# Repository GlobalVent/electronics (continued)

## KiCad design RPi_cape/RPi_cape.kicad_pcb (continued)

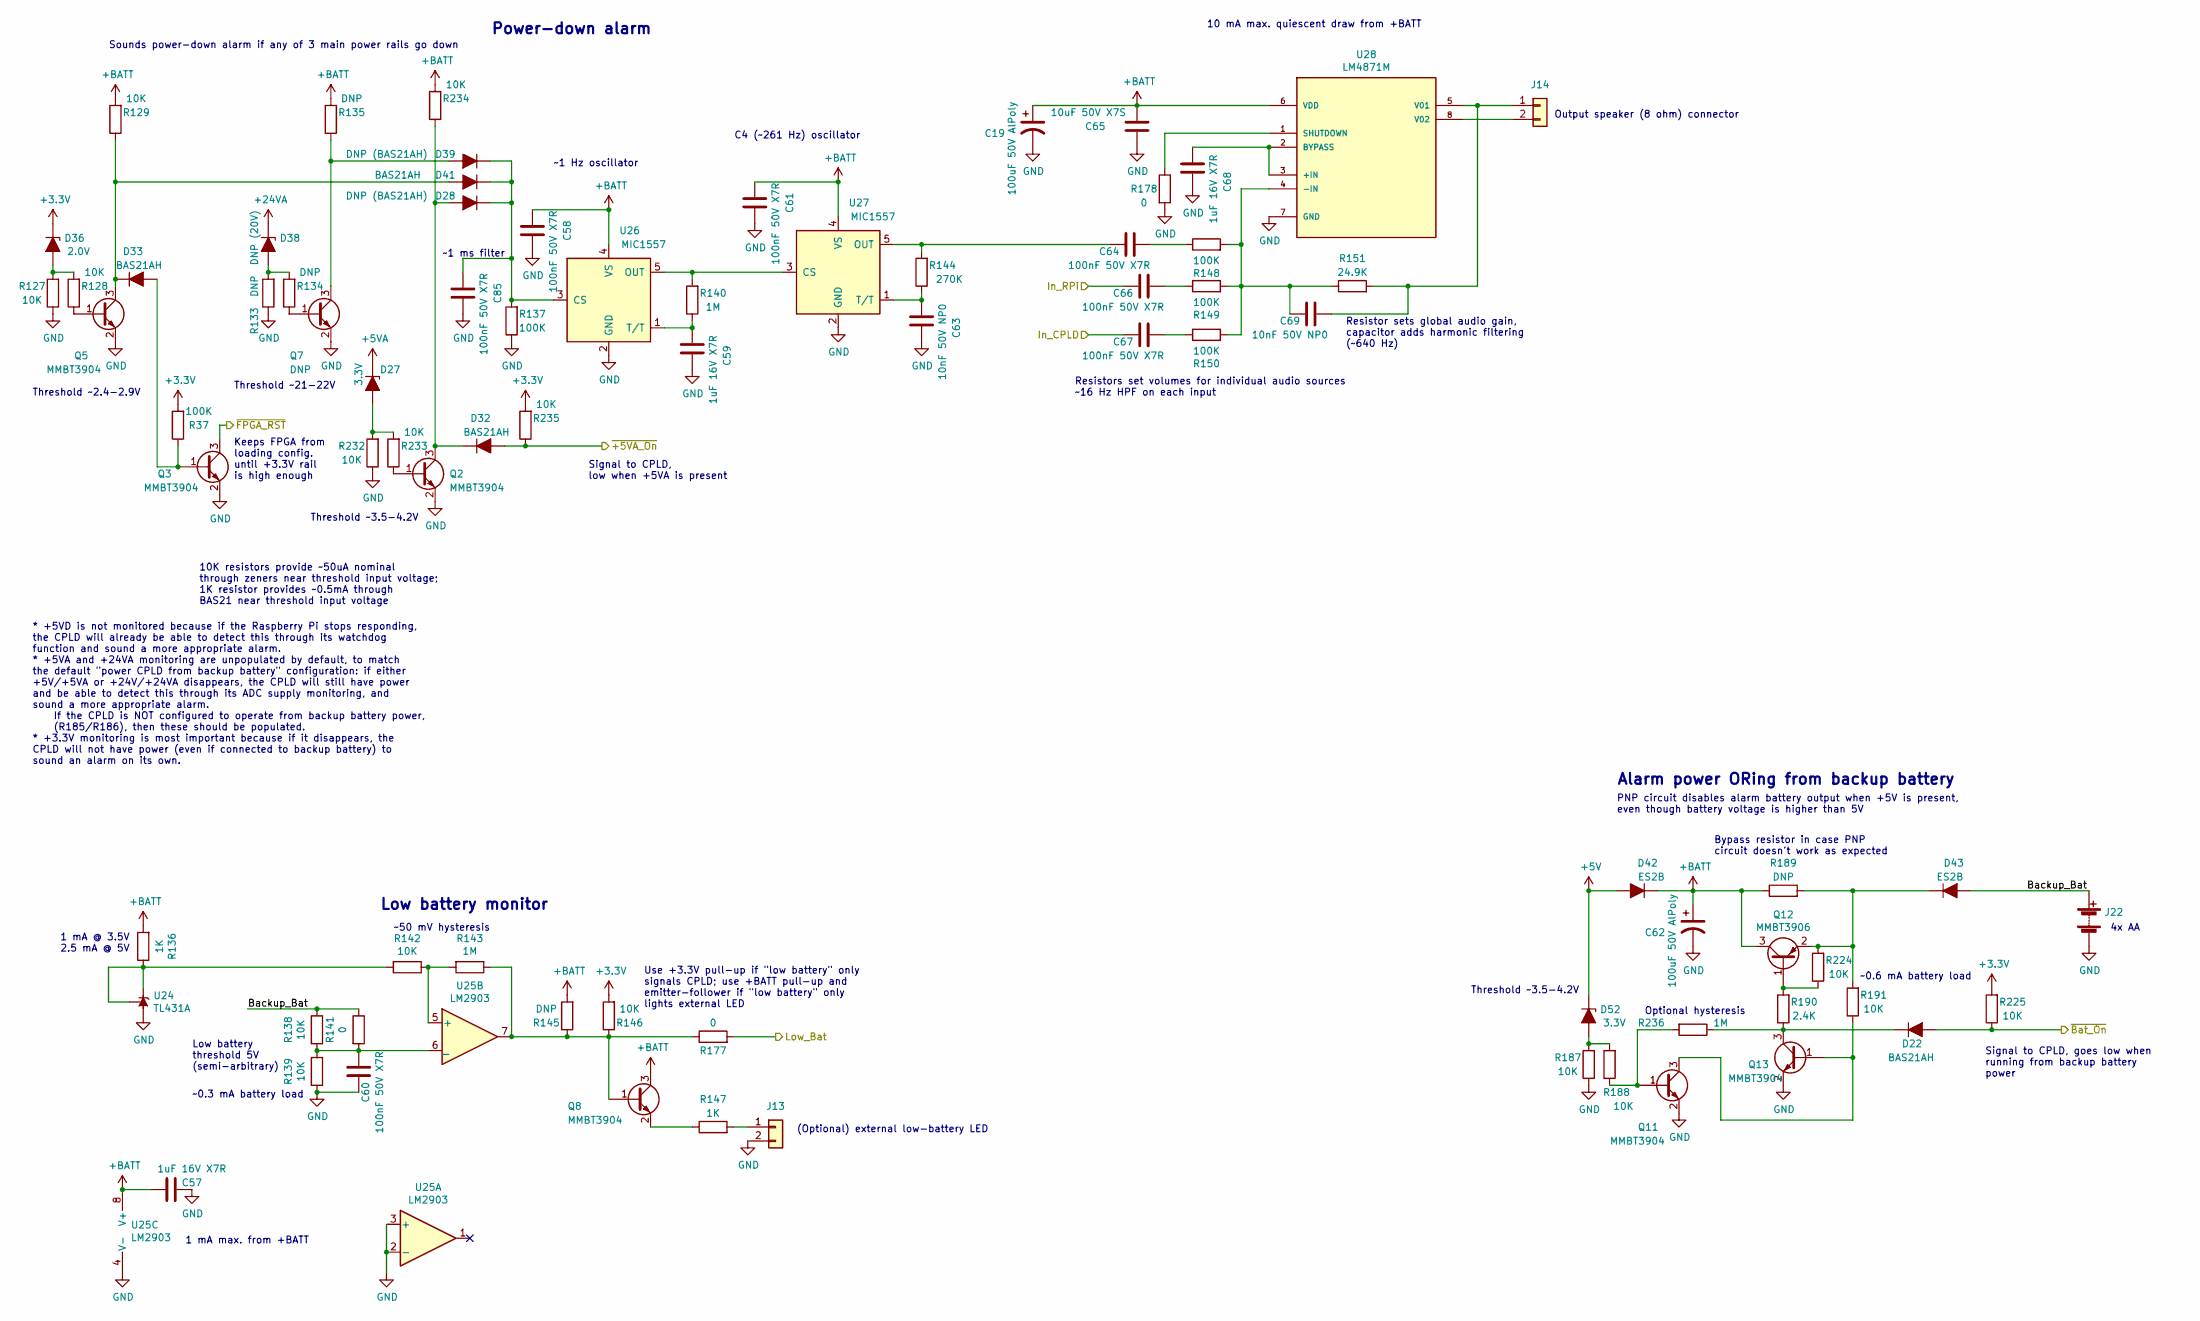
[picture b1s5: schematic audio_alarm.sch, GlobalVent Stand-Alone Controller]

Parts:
C19, C62: 100uF 50V AlPoly; CP_Elec_10x10.5; Part Number EEH-ZC1H101P
C57, C59, C68: 1uF 16V X7R; C_0805_2012Metric; Part Number C0805C105K4RACTU
C58, C60, C61, C64, C66, C67, C85: 100nF 50V X7R; C_0603_1608Metric; Part Number 06035C104JAT2A
C63, C69: 10nF 50V NP0; C_0603_1608Metric; Part Number GRM1885C1H103JA01D
C65: 10uF 50V X7S; C_1210_3225Metric; Part Number GCM32EC71H106KA03L
D22, D32, D33, D41: BAS21AH; D_SOD-323; Part Number BAS21AHT1G
D27, D52: 3.3V; D_SOD-123; Part Number MMSZ4684T1G
D28, D39: DNP (BAS21AH); D_SOD-323; Part Number BAS21AHT1G
D36: 2.0V; D_SOD-123; Part Number MMSZ4679T1G
D38: DNP (20V); D_SOD-123; Part Number MMSZ4707T1G
D42, D43: ES2B; D_SMA; Part Number ES2G-E3/52T
J13, J14: Conn_01x02; Connector_Spring_Phoenix_1985195; Part Number 1985195
J22: Conn_01x02; Connector_Spring_Phoenix_1985195; Part Number 9185195
Q2, Q3, Q5, Q8, Q11, Q13: MMBT3904; SOT-23; Part Number MMBT3904-7-F
Q7: DNP; SOT-23
Q12: MMBT3906; SOT-23; Part Number MMBT3906,215
R37, R137, R148, R149, R150: 100K; R_1206_3216Metric; Part Number RK73H2BTTD1003F
R127, R128, R129, R138, R139, R142, R146, R187, R188, R191, R224, R225, R232, R233, R234, R235: 10K; R_1206_3216Metric; Part Number RK73H2BTTD1002F
R133, R134, R135, R145, R189: DNP; R_1206_3216Metric
R136, R147: 1K; R_1206_3216Metric; Part Number RK73H2BTTD1001F
R140, R143, R236: 1M; R_1206_3216Metric; Part Number RK73H2BTTD1004F
R141, R177, R178: 0; R_1206_3216Metric; Part Number ERJ-8GEY0R00V
R144: 270K; R_1206_3216Metric; Part Number RK73H2BTTD2703F
R151: 24.9K; R_1206_3216Metric; Part Number RK73H2BTTD2492F
R190: 2.4K; R_1206_3216Metric; Part Number RK73H2BTTD2401F
U24: TL431A; SOT-23; Part Number TL431AQDBZR,215
U25: LM2903; VSSOP-8_3.0x3.0mm_P0.65mm; Part Number LM2903DGKR
U26, U27: MIC1557; SOT-23-5; Part Number MIC1557YM5-TR
U28: LM4871M; SOIC-8_3.9x4.9mm_P1.27mm; Part Number LM4871MX/NOPB

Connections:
+3V3: D36.1 (K), R37.2, R146.2, R225.2, R235.2; also elsewhere on the board
+5V: D42.2 (A), D52.1 (K); also elsewhere on the board
+24VA: D38.1 (K); also elsewhere on the board
+BATT: C19.1, C57.2, C58.2, C61.2, C62.1, C65.1, D42.1 (K), Q8.3 (C), Q12.3 (C), R129.2, R135.2, R136.2, R145.2, R189.1, R234.2, U25.8 (V+), U26.4 (VS), U27.4 (VS), U28.6 (VDD); also elsewhere on the board
/Auditory Alarm/Backup_Bat: D43.2 (A), J22.1 (+), R138.1, R141.1
/Auditory Alarm/Low_Bat: R177.2; also elsewhere on the board
/Auditory Alarm/~+5VA_On: D32.2 (A), R235.1; also elsewhere on the board
/Auditory Alarm/~Bat_On: D22.2 (A), R225.1; also elsewhere on the board
/Auditory Alarm/~FPGA_RST: Q3.3 (C); also elsewhere on the board
/CPLD_Alarm_Spkr: C67.1; also elsewhere on the board
/RPi_Alarm_Spkr: C66.1; also elsewhere on the board
unnamed: C59.2, R140.1, U26.1 (T/T)
unnamed: C60.2, R138.2, R139.1, R141.2, U25.6 (_)
unnamed: C63.2, R144.1, U27.1 (T/T)
unnamed: C64.1, R144.2, U27.5 (OUT)
unnamed: C64.2, R148.1
unnamed: C66.2, R149.1
unnamed: C67.2, R150.1
unnamed: C68.2, U28.2 (BYPASS), U28.3 (+IN)
unnamed: C69.1, R148.2, R149.2, R150.2, R151.1, U28.4 (-IN)
unnamed: C69.2, J14.1, R151.2, U28.5 (V01)
unnamed: C85.2, D28.1 (K), D39.1 (K), D41.1 (K), R137.2, U26.3 (CS)
unnamed: D22.1 (K), Q13.3 (C), R190.1, R236.1
unnamed: D27.2 (A), R232.2, R233.2
unnamed: D28.2 (A), D32.1 (K), Q2.3 (C), R234.1
unnamed: D33.1 (K), D41.2 (A), Q5.3 (C), R129.1
unnamed: D33.2 (A), Q3.1 (B), R37.1
unnamed: D36.2 (A), R127.2, R128.2
unnamed: D38.2 (A), R133.2, R134.2
unnamed: D39.2 (A), Q7.3 (C), R135.1
unnamed: D43.1 (K), Q12.2 (E), R189.2, R191.2, R224.2
unnamed: D52.2 (A), R187.2, R188.2
unnamed: J13.1, R147.2
unnamed: J14.2, U28.8 (V02)
unnamed: Q2.1 (B), R233.1
unnamed: Q5.1 (B), R128.1
unnamed: Q7.1 (B), R134.1
unnamed: Q8.1 (B), R143.1, R145.1, R146.1, R177.1, U25.7
unnamed: Q8.2 (E), R147.1
unnamed: Q11.1 (B), R188.1, R236.2
unnamed: Q11.3 (C), Q13.1 (B), R191.1
unnamed: Q12.1 (B), R190.2, R224.1
unnamed: R136.1, R142.2, U24.1 (K), U24.2 (REF)
unnamed: R140.2, U26.5 (OUT), U27.3 (CS)
unnamed: R142.1, R143.2, U25.5 (+)
unnamed: R178.1, U28.1 (SHUTDOWN)

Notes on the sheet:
1 mA max. from +BATT
1 mA @ 3.5V 2.5 mA @ 5V
Power-down alarm
Low battery monitor
Output speaker (8 ohm) connector
Resistors set volumes for individual audio sources ~~16 Hz HPF on each input
Resistor sets global audio gain, capacitor adds harmonic filtering (~~640 Hz)
C4 (~~261 Hz) oscillator
~~1 Hz oscillator
Threshold ~~2.4-2.9V
Threshold ~~21-22V
Sounds power-down alarm if any of 3 main power rails go down
Low battery threshold 5V (semi-arbitrary)
Alarm power ORing from backup battery
~~50 mV hysteresis
(Optional) external low-battery LED
Use +3.3V pull-up if "low battery" only signals CPLD; use +BATT pull-up and emitter-follower if "low battery" only lights external LED
Bypass resistor in case PNP circuit doesn't work as expected
PNP circuit disables alarm battery output when +5V is present, even though battery voltage is higher than 5V
Threshold ~~3.5-4.2V
* +5VD is not monitored because if the Raspberry Pi stops responding, the CPLD will already be able to detect this through its watchdog function and sound a more appropriate alarm. * +5VA and +24VA monitoring are unpopulated by default, to match the default "power CPLD from backup battery" configur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
10 mA max. quiescent draw from +BATT
~~0.6 mA battery load
~~0.3 mA battery load
Signal to CPLD, goes low when running from backup battery power
10K resistors provide ~~50uA nominal through zeners near threshold input voltage; 1K resistor provides ~~0.5mA through BAS21 near threshold input voltage
Signal to CPLD, low when +5VA is present
Optional hysteresis
~~1 ms filter
Keeps FPGA from loading config. until +3.3V rail is high enough
4x AA

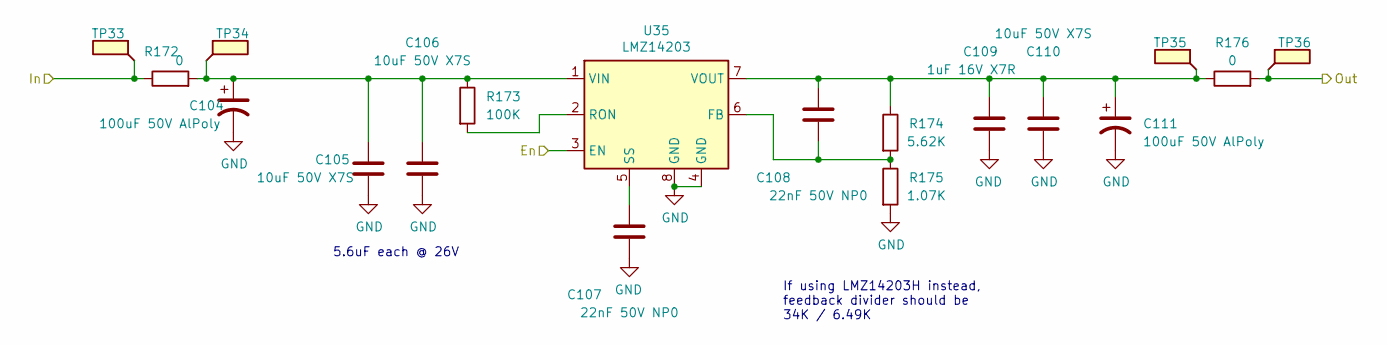
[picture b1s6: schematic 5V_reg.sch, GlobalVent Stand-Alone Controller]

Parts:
C96, C103: 100uF 50V AlPoly; CP_Elec_10x10.5; Part Number EEH-ZC1H101P
C97, C98, C102: 10uF 50V X7S; C_1210_3225Metric; Part Number GCM32EC71H106KA03L
C99, C100: 22nF 50V NP0; C_0805_2012Metric; Part Number GCM21B5C1H223JA16L
C101: 1uF 16V X7R; C_0805_2012Metric; Part Number C0805C105K4RACTU
R167, R171: 0; R_1206_3216Metric; Part Number ERJ-8GEY0R00V
R168: 100K; R_1206_3216Metric; Part Number RK73H2BTTD1003F
R169: 5.62K; R_1206_3216Metric; Part Number RK73H2BTTD5621F
R170: 1.07K; R_1206_3216Metric; Part Number RK73H2BTTD1071F
TP29, TP30, TP31, TP32: TestPoint_Flag; TestPoint_Keystone_5019_Minature; Part Number 5019
U34: LMZ14203; TI_TO-PMOD-7; Part Number LMZ14203TZX-ADJ/NOPB

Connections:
+5VD: R171.2, TP32.1; also elsewhere on the board
+24V: R167.1, TP29.1; also elsewhere on the board
/RPi_En: U34.3 (EN); also elsewhere on the board
unnamed: C96.1, C97.1, C98.1, R167.2, R168.1, TP30.1, U34.1 (VIN)
unnamed: C99.2, U34.5 (SS)
unnamed: C100.1, R169.2, R170.1, U34.6 (FB)
unnamed: C100.2, C101.2, C102.1, C103.1, R169.1, R171.1, TP31.1, U34.7 (VOUT)
unnamed: R168.2, U34.2 (RON)

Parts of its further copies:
C104, C111: 100uF 50V AlPoly; CP_Elec_10x10.5; Part Number EEH-ZC1H101P
C105, C106, C110: 10uF 50V X7S; C_1210_3225Metric; Part Number GCM32EC71H106KA03L
C107, C108: 22nF 50V NP0; C_0805_2012Metric; Part Number GCM21B5C1H223JA16L
C109: 1uF 16V X7R; C_0805_2012Metric; Part Number C0805C105K4RACTU
R172, R176: 0; R_1206_3216Metric; Part Number ERJ-8GEY0R00V
R173: 100K; R_1206_3216Metric; Part Number RK73H2BTTD1003F
R174: 5.62K; R_1206_3216Metric; Part Number RK73H2BTTD5621F
R175: 1.07K; R_1206_3216Metric; Part Number RK73H2BTTD1071F
TP33, TP34, TP35, TP36: TestPoint_Flag; TestPoint_Keystone_5019_Minature; Part Number 5019
U35: LMZ14203; TI_TO-PMOD-7; Part Number LMZ14203TZX-ADJ/NOPB

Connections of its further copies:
+5V: R176.2, TP36.1; also elsewhere on the board
+24V: R172.1, TP33.1; also elsewhere on the board
/5V Regulator (other)/En: U35.3 (EN); also elsewhere on the board
unnamed: C104.1, C105.1, C106.1, R172.2, R173.1, TP34.1, U35.1 (VIN)
unnamed: C107.2, U35.5 (SS)
unnamed: C108.1, R174.2, R175.1, U35.6 (FB)
unnamed: C108.2, C109.2, C110.1, C111.1, R174.1, R176.1, TP35.1, U35.7 (VOUT)
unnamed: R173.2, U35.2 (RON)

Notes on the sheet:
If using LMZ14203H instead, feedback divider should be 34K / 6.49K
5.6uF each @ 26V

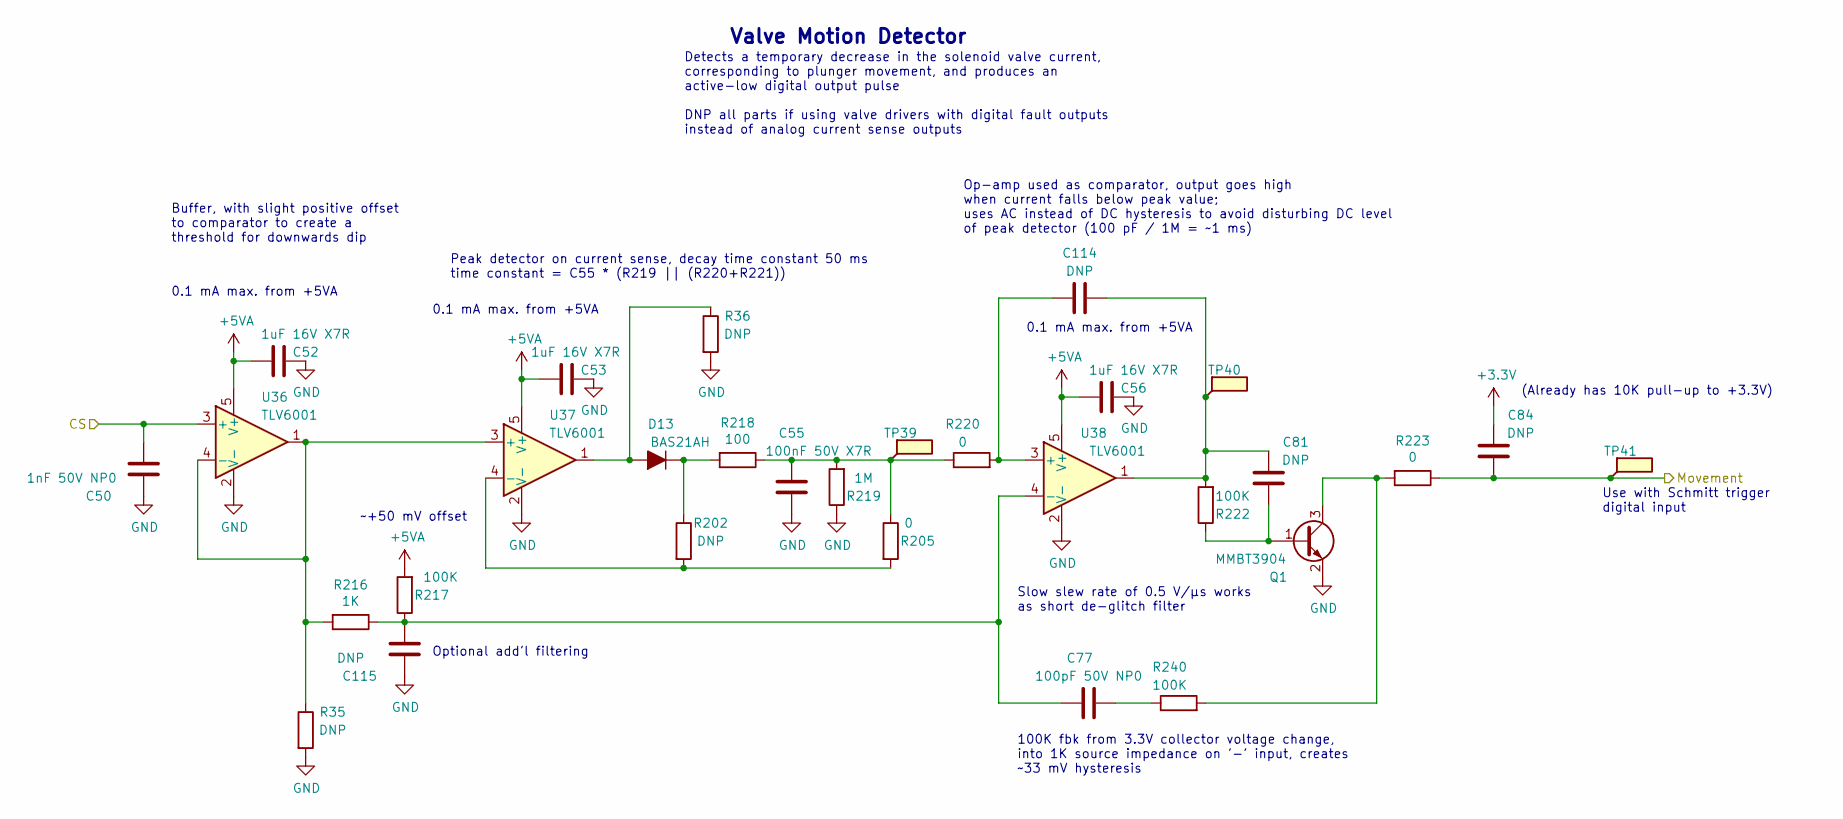
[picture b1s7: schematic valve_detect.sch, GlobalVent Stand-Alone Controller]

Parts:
C50: 1nF 50V NP0; C_0603_1608Metric; Part Number 06035A102JAT2A
C52, C55: 1uF 16V X7R; C_0805_2012Metric; Part Number C0805C105K4RACTU
C53: 100nF 50V X7R; C_0603_1608Metric; Part Number 06035C104JAT2A
C56, C81, C114, C115: DNP; C_0603_1608Metric
C77: 100pF 50V NP0; C_0603_1608Metric; Part Number C0603C101J5GACTU
D13: BAS21AH; D_SOD-323; Part Number BAS21AHT1G
Q1: MMBT3904; SOT-23; Part Number MMBT3904-7-F
R35, R36, R202: DNP; R_1206_3216Metric
R205, R219, R220: 0; R_1206_3216Metric; Part Number ERJ-8GEY0R00V
R216: 100; R_1206_3216Metric; Part Number RK73H2BTTD1000F
R217: 1M; R_1206_3216Metric; Part Number RK73H2BTTD1004F
R218, R240: 100K; R_1206_3216Metric; Part Number RK73H2BTTD1003F
TP39, TP40, TP41: TestPoint_Flag; TestPoint_Keystone_5019_Minature; Part Number 5019
U36, U37: TLV6001; SOT-23-5; Part Number TLV6001IDBVR

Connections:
unnamed: C77.2, R240.1

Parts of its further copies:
C84: DNP; C_0603_1608Metric
R222: 100K; R_1206_3216Metric; Part Number RK73H2BTTD1003F
R223: 0; R_1206_3216Metric; Part Number ERJ-8GEY0R00V
U38: TLV6001; SOT-23-5; Part Number TLV6001IDBVR

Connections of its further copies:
+3V3: C84.1; also elsewhere on the board

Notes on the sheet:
0.1 mA max. from +5VA
Detects a temporary decrease in the solenoid valve current, corresponding to plunger movement, and produces an active-low digital output pulse DNP all parts if using valve drivers with digital fault outputs instead of analog current sense outputs
Use with Schmitt trigger digital input
Peak detector on current sense, decay time constant 50 ms time constant = C55 * (R219 || (R220+R221))
Op-amp used as comparator, output goes high when current falls below peak value; uses AC instead of DC hysteresis to avoid disturbing DC level of peak detector (100 pF / 1M = ~~1 ms)
Buffer, with slight positive offset to comparator to create a threshold for downwards dip
~~+50 mV offset
Valve Motion Detector
(Already has 10K pull-up to +3.3V)
Optional add'l filtering
Slow slew rate of 0.5 V/µs works as short de-glitch filter
100K fbk from 3.3V collector voltage change, into 1K source impedance on '-' input, creates ~~33 mV hysteresis

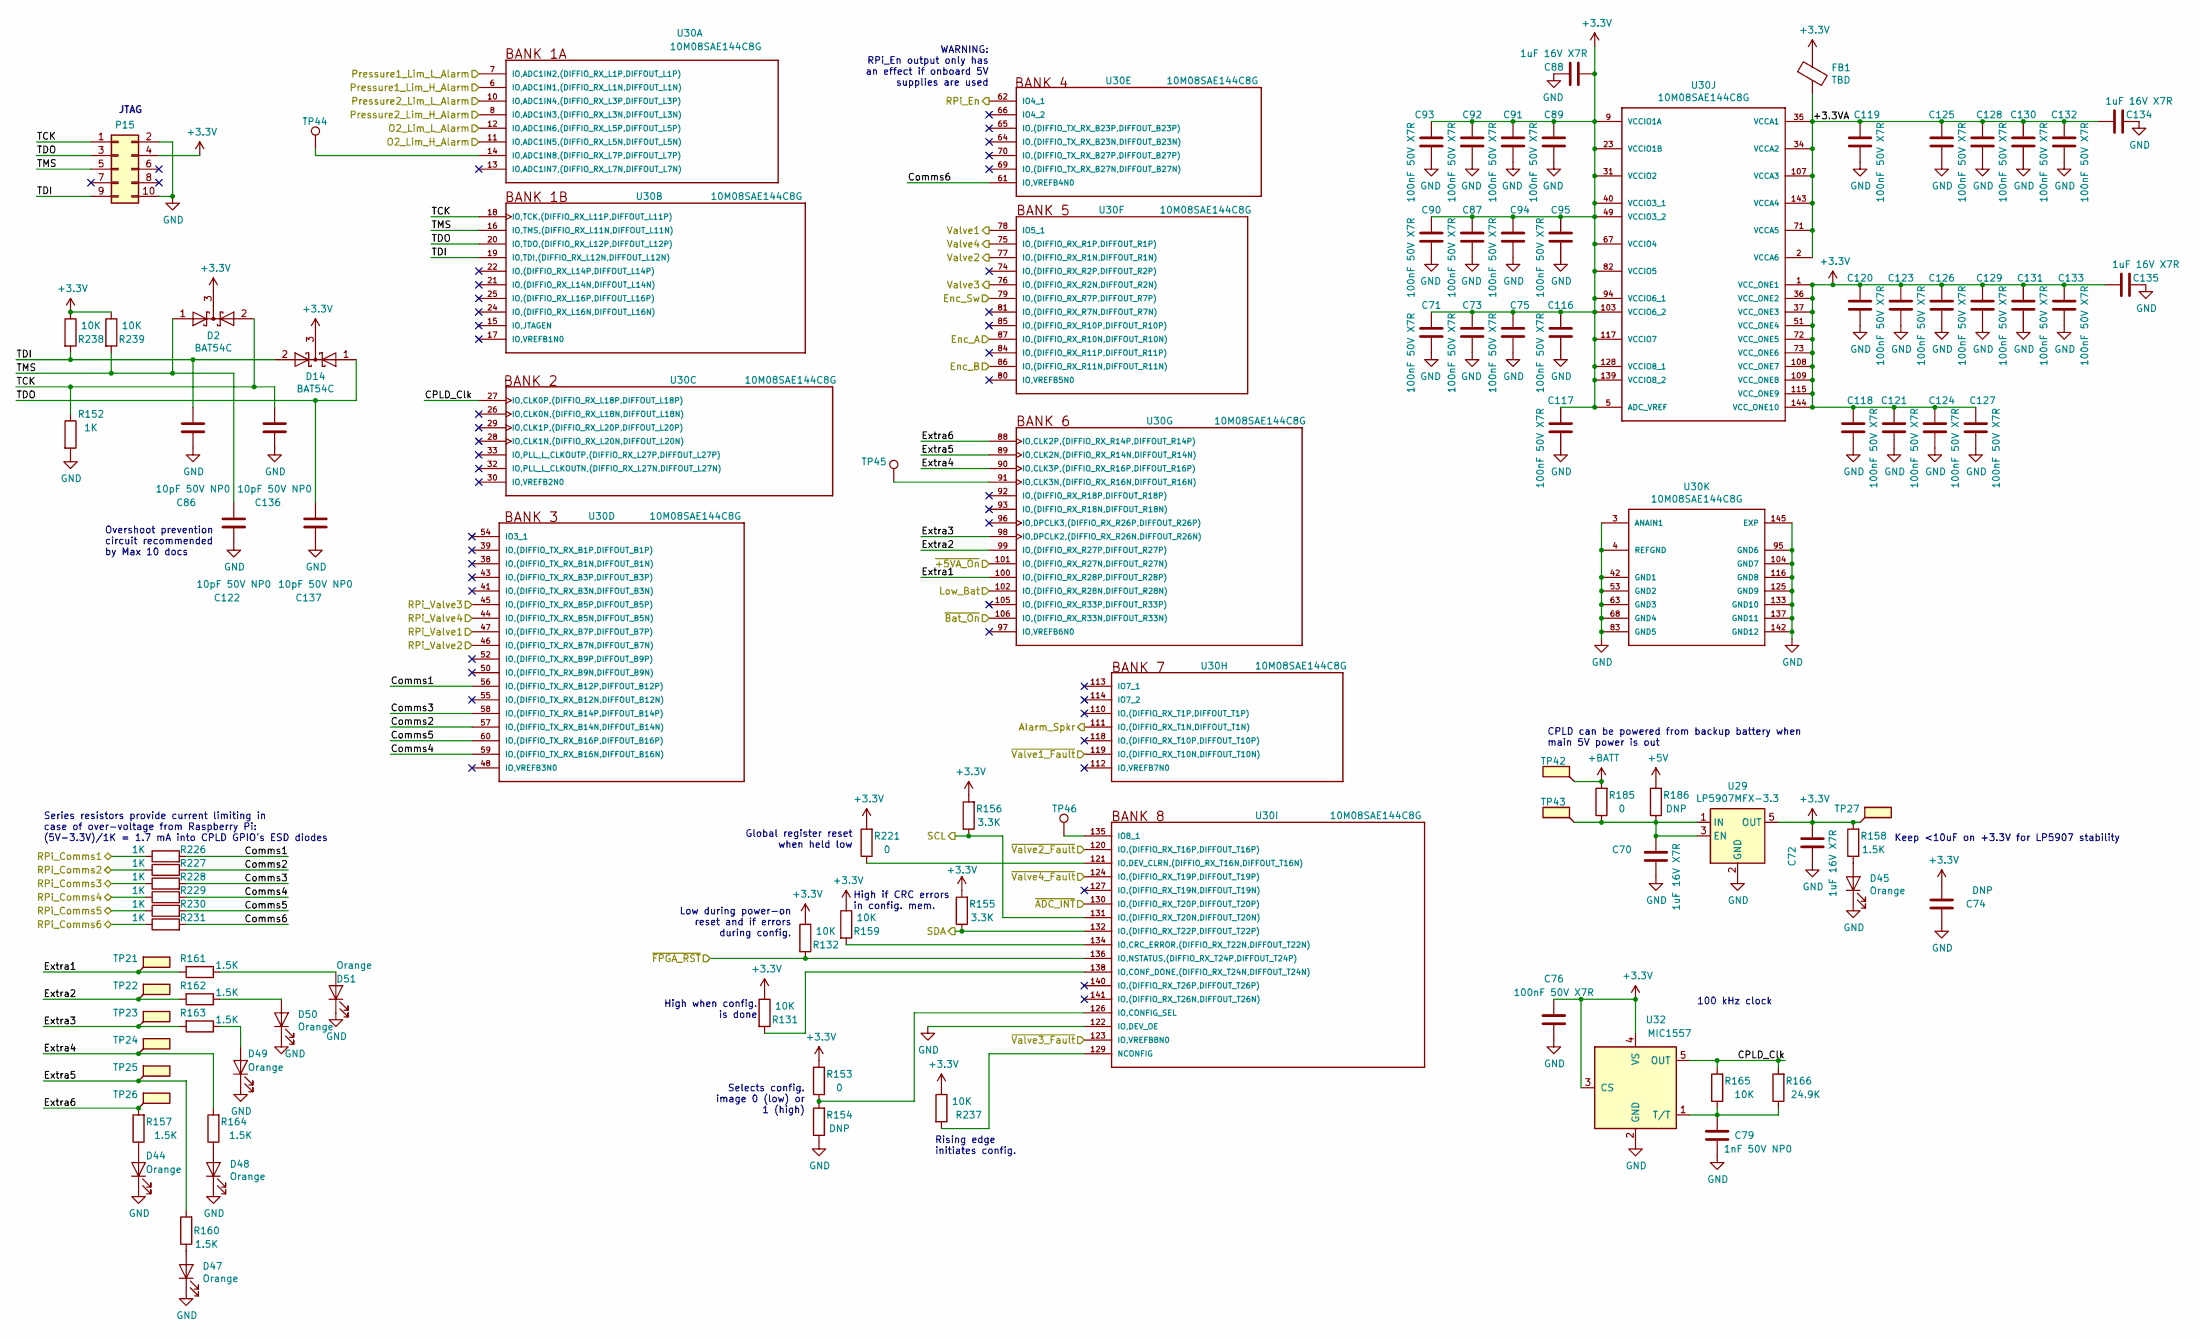
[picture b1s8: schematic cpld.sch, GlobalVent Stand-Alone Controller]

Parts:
C70, C72, C88, C134, C135: 1uF 16V X7R; C_0805_2012Metric; Part Number C0805C105K4RACTU
C71, C73, C75, C76, C87, C89, C90, C91, C92, C93, C94, C95, C116, C117, C118, C119, C120, C121, C123, C124, C125, C126, C127, C128, C129, C130, C131, C132, C133: 100nF 50V X7R; C_0603_1608Metric; Part Number 06035C104JAT2A
C74: DNP; C_1210_3225Metric
C79: 1nF 50V NP0; C_0603_1608Metric; Part Number 06035A102JAT2A
C86, C122, C136, C137: 10pF 50V NP0; C_0603_1608Metric
D2, D14: BAT54C; SOT-23; Part Number BAT54C-7-F
D44, D45, D47, D48, D49, D50, D51: Orange; LED_0805_2012Metric; Part Number HSMD-C170
FB1: TBD; L_0805_2012Metric
P15: Conn_02x05_Odd_Even; PinHeader_2x05_P2.54mm_Vertical
R131, R132, R159, R165, R237, R238, R239: 10K; R_1206_3216Metric; Part Number RK73H2BTTD1002F
R152, R226, R227, R228, R229, R230, R231: 1K; R_1206_3216Metric; Part Number RK73H2BTTD1001F
R153, R185, R221: 0; R_1206_3216Metric; Part Number ERJ-8GEY0R00V
R154, R186: DNP; R_1206_3216Metric
R155, R156: 3.3K; R_1206_3216Metric; Part Number RK73H2BTTD3301F
R157, R158, R160, R161, R162, R163, R164: 1.5K; R_1206_3216Metric; Part Number RK73H2BTTD1501F
R166: 24.9K; R_1206_3216Metric; Part Number RK73H2BTTD2492F
TP21, TP22, TP23, TP24, TP25, TP26, TP27, TP42, TP43: TestPoint_Flag; TestPoint_Keystone_5019_Minature; Part Number 5019
TP44, TP45, TP46: TestPoint; TestPoint_Pad_1.0x1.0mm
U29: LP5907MFX-3.3; SOT-23-5; Part Number LP5907MFX-3.3/NOPB
U30: 10M08SAE144C8G; LQFP50P2200X2200X160-145N; Part Number 10M08SAE144C8G
U32: MIC1557; SOT-23-5; Part Number MIC1557YM5-TR

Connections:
+3V3: C71.2, C72.2, C73.2, C74.1, C75.2, C76.2, C87.2, C88.2, C89.2, C90.2, C91.2, C92.2, C93.2, C94.2, C95.2, C116.2, C117.2, C118.2, C120.2, C121.2, C123.2, C124.2, C126.2, C127.2, C129.2, C131.2, C133.2, C135.2, D2.3 (K), D14.3 (K), FB1.1, P15.4, R131.1, R132.1, R153.2, R155.2, R156.2, R158.2, R159.1, R221.2, R237.1, R238.1, R239.1, TP27.1, U29.5 (OUT), U30.1 (VCC_ONE1), U30.5 (ADC_VREF), U30.9 (VCCIO1A), U30.23 (VCCIO1B), U30.31 (VCCIO2), U30.36 (VCC_ONE2), U30.37 (VCC_ONE3), U30.40 (VCCIO3_1), U30.49 (VCCIO3_2), U30.51 (VCC_ONE4), U30.67 (VCCIO4), U30.72 (VCC_ONE5), U30.73 (VCC_ONE6), U30.82 (VCCIO5), U30.94 (VCCIO6_1), U30.103 (VCCIO6_2), U30.108 (VCC_ONE7), U30.109 (VCC_ONE8), U30.115 (VCC_ONE9), U30.117 (VCCIO7), U30.128 (VCCIO8_1), U30.139 (VCCIO8_2), U30.144 (VCC_ONE10), U32.3 (CS), U32.4 (VS); also elsewhere on the board
+5V: R186.2; also elsewhere on the board
+BATT: R185.2, TP42.1; also elsewhere on the board
/Auditory Alarm/Low_Bat: U30.102 (IO,(DIFFIO_RX_R28N,DIFFOUT_R28N)); also elsewhere on the board
/Auditory Alarm/~+5VA_On: U30.101 (IO,(DIFFIO_RX_R27N,DIFFOUT_R27N)); also elsewhere on the board
/Auditory Alarm/~Bat_On: U30.106 (IO,(DIFFIO_RX_R33N,DIFFOUT_R33N)); also elsewhere on the board
/Auditory Alarm/~FPGA_RST: R132.2, U30.136 (IO,NSTATUS,(DIFFIO_RX_T24P,DIFFOUT_T24P)); also elsewhere on the board
/CPLD/+3.3VA: C119.2, C125.2, C128.2, C130.2, C132.2, C134.2, FB1.2, U30.2 (VCCA6), U30.34 (VCCA2), U30.35 (VCCA1), U30.71 (VCCA5), U30.107 (VCCA3), U30.143 (VCCA4)
/CPLD/CPLD_Clk: R165.2, R166.2, U30.27 (IO,CLK0P,(DIFFIO_RX_L18P,DIFFOUT_L18P)), U32.5 (OUT)
/CPLD/Comms1: R226.2, U30.56 (IO,(DIFFIO_TX_RX_B12P,DIFFOUT_B12P))
/CPLD/Comms2: R227.2, U30.57 (IO,(DIFFIO_TX_RX_B14N,DIFFOUT_B14N))
/CPLD/Comms3: R228.2, U30.58 (IO,(DIFFIO_TX_RX_B14P,DIFFOUT_B14P))
/CPLD/Comms4: R229.2, U30.59 (IO,(DIFFIO_TX_RX_B16N,DIFFOUT_B16N))
/CPLD/Comms5: R230.2, U30.60 (IO,(DIFFIO_TX_RX_B16P,DIFFOUT_B16P))
/CPLD/Comms6: R231.2, U30.61 (IO,VREFB4N0)
/CPLD/Extra1: R161.2, TP21.1, U30.100 (IO,(DIFFIO_RX_R28P,DIFFOUT_R28P))
/CPLD/Extra2: R162.2, TP22.1, U30.99 (IO,(DIFFIO_RX_R27P,DIFFOUT_R27P))
/CPLD/Extra3: R163.2, TP23.1, U30.98 (IO,DPCLK2,(DIFFIO_RX_R26N,DIFFOUT_R26N))
/CPLD/Extra4: R164.2, TP24.1, U30.90 (IO,CLK3P,(DIFFIO_RX_R16P,DIFFOUT_R16P))
/CPLD/Extra5: R160.2, TP25.1, U30.89 (IO,CLK2N,(DIFFIO_RX_R14N,DIFFOUT_R14N))
/CPLD/Extra6: R157.2, TP26.1, U30.88 (IO,CLK2P,(DIFFIO_RX_R14P,DIFFOUT_R14P))
/CPLD/TCK: C136.2, D2.2 (A), P15.1, R152.1, U30.18 (IO,TCK,(DIFFIO_RX_L11P,DIFFOUT_L11P))
/CPLD/TDI: C86.2, D14.2 (A), P15.9, R238.2, U30.19 (IO,TDI,(DIFFIO_RX_L12N,DIFFOUT_L12N))
/CPLD/TDO: C137.2, D14.1 (A), P15.3, U30.20 (IO,TDO,(DIFFIO_RX_L12P,DIFFOUT_L12P))
/CPLD/TMS: C122.2, D2.1 (A), P15.5, R239.2, U30.16 (IO,TMS,(DIFFIO_RX_L11N,DIFFOUT_L11N))
/CPLD/~ADC_INT: U30.130 (IO,(DIFFIO_RX_T20P,DIFFOUT_T20P)); also elsewhere on the board
/CPLD_Alarm_Spkr: U30.111 (IO,(DIFFIO_RX_T1N,DIFFOUT_T1N)); also elsewhere on the board
/CPLD_SCL: R156.1, U30.131 (IO,(DIFFIO_RX_T20N,DIFFOUT_T20N)); also elsewhere on the board
/CPLD_SDA: R155.1, U30.132 (IO,(DIFFIO_RX_T22P,DIFFOUT_T22P)); also elsewhere on the board
/CPLD_valve1: U30.78 (IO5_1); also elsewhere on the board
/CPLD_valve2: U30.77 (IO,(DIFFIO_RX_R1N,DIFFOUT_R1N)); also elsewhere on the board
/CPLD_valve3: U30.76 (IO,(DIFFIO_RX_R2N,DIFFOUT_R2N)); also elsewhere on the board
/CPLD_valve4: U30.75 (IO,(DIFFIO_RX_R1P,DIFFOUT_R1P)); also elsewhere on the board
/Comms1: R226.1; also elsewhere on the board
/Comms2: R227.1; also elsewhere on the board
/Comms3: R228.1; also elsewhere on the board
/Comms4: R229.1; also elsewhere on the board
/Comms5: R230.1; also elsewhere on the board
/Comms6: R231.1; also elsewhere on the board
/Enc_A: U30.87 (IO,(DIFFIO_RX_R10N,DIFFOUT_R10N)); also elsewhere on the board
/Enc_B: U30.86 (IO,(DIFFIO_RX_R11N,DIFFOUT_R11N)); also elsewhere on the board
/Enc_Sw: U30.79 (IO,(DIFFIO_RX_R7P,DIFFOUT_R7P)); also elsewhere on the board
/O2_Lim_H_Alarm: U30.11 (IO,ADC1IN5,(DIFFIO_RX_L5N,DIFFOUT_L5N)); also elsewhere on the board
/O2_Lim_L_Alarm: U30.12 (IO,ADC1IN6,(DIFFIO_RX_L5P,DIFFOUT_L5P)); also elsewhere on the board
/Pressure1_Lim_H_Alarm: U30.6 (IO,ADC1IN1,(DIFFIO_RX_L1N,DIFFOUT_L1N)); also elsewhere on the board
/Pressure1_Lim_L_Alarm: U30.7 (IO,ADC1IN2,(DIFFIO_RX_L1P,DIFFOUT_L1P)); also elsewhere on the board
/Pressure2_Lim_H_Alarm: U30.8 (IO,ADC1IN3,(DIFFIO_RX_L3N,DIFFOUT_L3N)); also elsewhere on the board
/Pressure2_Lim_L_Alarm: U30.10 (IO,ADC1IN4,(DIFFIO_RX_L3P,DIFFOUT_L3P)); also elsewhere on the board
/RPi_En: U30.62 (IO4_1); also elsewhere on the board
/RPi_valve1: U30.47 (IO,(DIFFIO_TX_RX_B7P,DIFFOUT_B7P)); also elsewhere on the board
/RPi_valve2: U30.46 (IO,(DIFFIO_TX_RX_B7N,DIFFOUT_B7N)); also elsewhere on the board
/RPi_valve3: U30.45 (IO,(DIFFIO_TX_RX_B5P,DIFFOUT_B5P)); also elsewhere on the board
/RPi_valve4: U30.44 (IO,(DIFFIO_TX_RX_B5N,DIFFOUT_B5N)); also elsewhere on the board
/~Valve1_Fault: U30.119 (IO,(DIFFIO_RX_T10N,DIFFOUT_T10N)); also elsewhere on the board
/~Valve2_Fault: U30.120 (IO,(DIFFIO_RX_T16P,DIFFOUT_T16P)); also elsewhere on the board
/~Valve3_Fault: U30.123 (IO,VREFB8N0); also elsewhere on the board
unnamed: C70.2, R185.1, R186.1, TP43.1, U29.1 (IN), U29.3 (EN)
unnamed: C79.2, R165.1, R166.1, U32.1 (T/T)
unnamed: D44.2 (A), R157.1
unnamed: D45.2 (A), R158.1
unnamed: D47.2 (A), R160.1
unnamed: D48.2 (A), R164.1
unnamed: D49.2 (A), R163.1
unnamed: D50.2 (A), R162.1
unnamed: D51.2 (A), R161.1
unnamed: R131.2, U30.138 (IO,CONF_DONE,(DIFFIO_RX_T24N,DIFFOUT_T2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)
unnamed: R153.1, R154.2, U30.126 (IO,CONFIG_SEL)
unnamed: R159.2, U30.134 (IO,CRC_ERROR,(DIFFIO_RX_T22N,DIFFOUT_T2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)
unnamed: R221.1, U30.121 (IO,DEV_CLRN,(DIFFIO_RX_T16N,DIFFOUT_T16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)
unnamed: R237.2, U30.129 (NCONFIG)
unnamed: TP44.1, U30.14 (IO,ADC1IN8,(DIFFIO_RX_L7P,DIFFOUT_L7P))
unnamed: TP45.1, U30.91 (IO,CLK3N,(DIFFIO_RX_R16N,DIFFOUT_R16N))
unnamed: TP46.1, U30.135 (IO8_1)

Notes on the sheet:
JTAG
Keep <10uF on +3.3V for LP5907 stability
WARNING: RPi_En output only has an effect if onboard 5V supplies are used
100 kHz clock
CPLD can be powered from backup battery when main 5V power is out
Series resistors provide current limiting in case of over-voltage from Raspberry Pi: (5V-3.3V)/1K = 1.7 mA into CPLD GPIO's ESD diodes
High if CRC errors in config. mem.
High when config. is done
Selects config. image 0 (low) or 1 (high)
Global register reset when held low
Rising edge initiates config.
Low during power-on reset and if errors during config.
Overshoot prevention circuit recommended by Max 10 docs

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
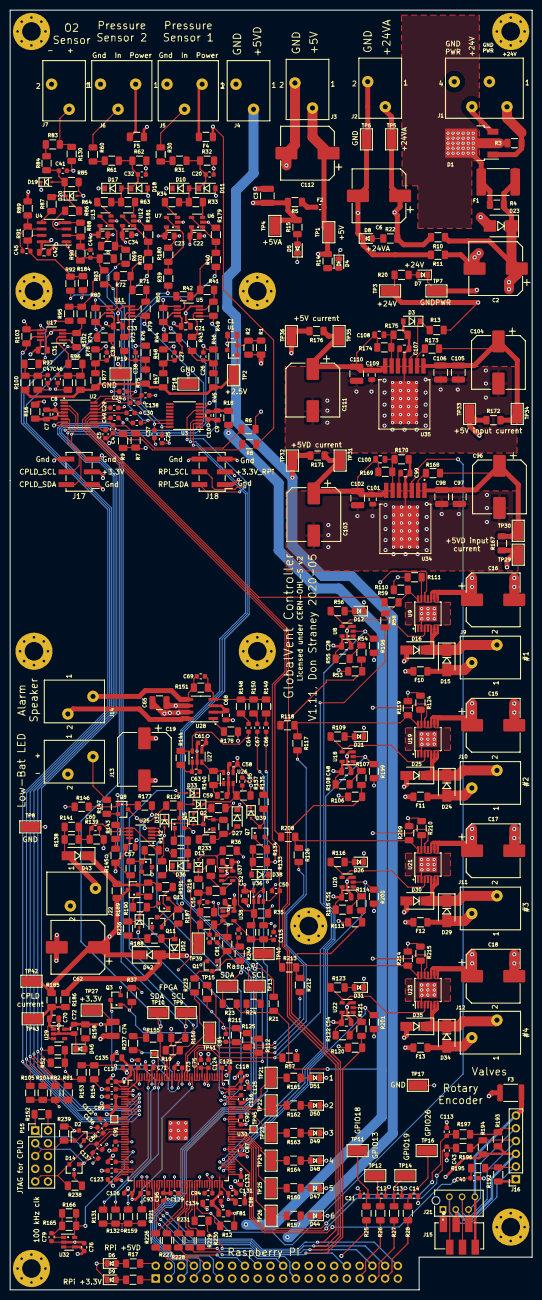
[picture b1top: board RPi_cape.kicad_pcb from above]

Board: 4 copper layers, 104.0 x 255.0 mm, 535 parts (1 on the bottom side), 250 nets.

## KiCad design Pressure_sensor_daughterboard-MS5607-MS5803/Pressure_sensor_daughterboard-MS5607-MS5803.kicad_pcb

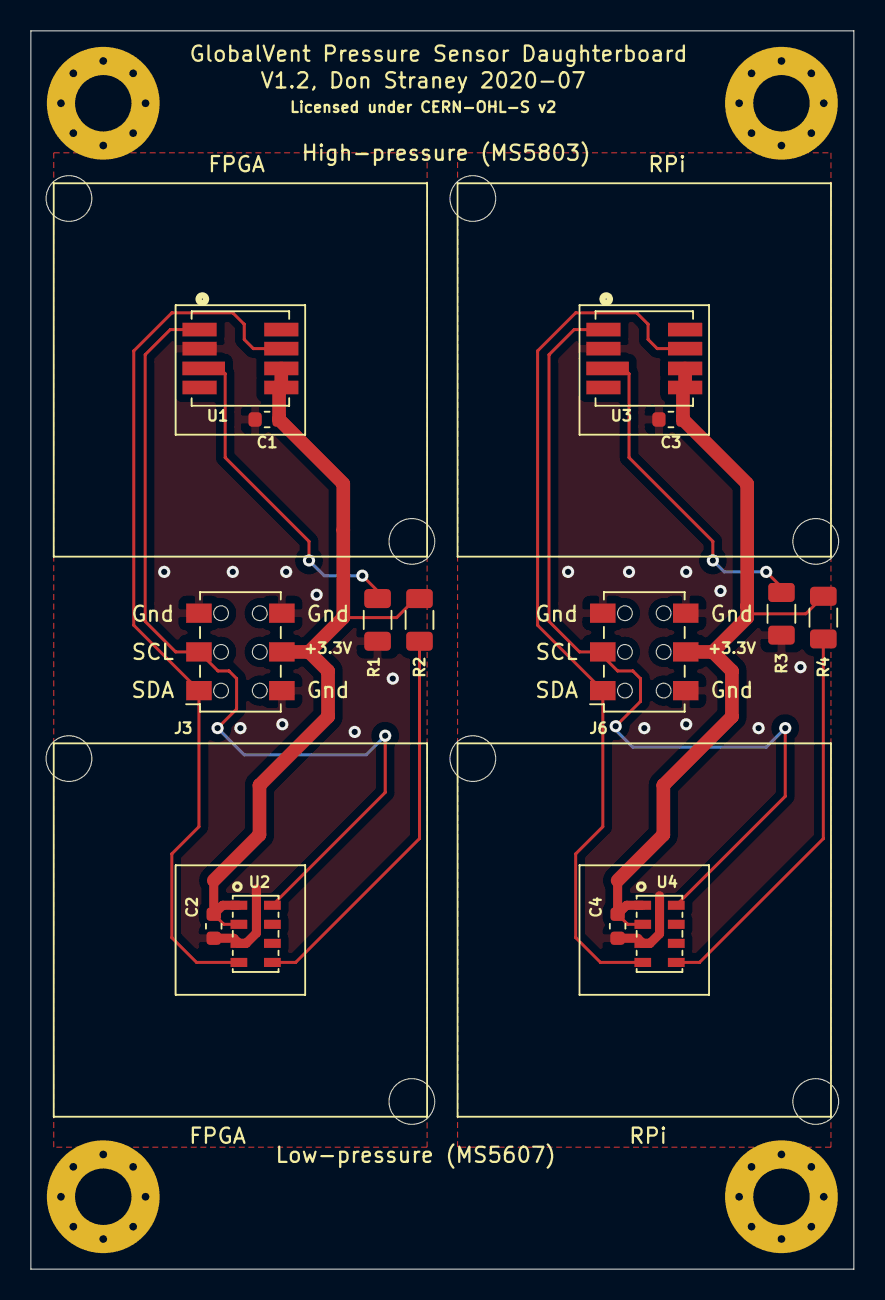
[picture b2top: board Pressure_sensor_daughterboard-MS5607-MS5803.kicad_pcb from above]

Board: 2 copper layers, 54.0 x 81.2 mm, 22 parts (0 on the bottom side), 10 nets.

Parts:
C1, C2, C3, C4: 100nF 50V X7R; C_0603_1608Metric
H1, H2, H3, H4: #6; MountingHole_3.7mm_Pad_Via
J1, J2, J4, J5: Pressure_sensor_barb; Sensor_cap_glued_8.5x8.5
J3, J6: Conn_02x03_Odd_Even; Samtec_HLE-103-02-xxx-DV-BE_2x03_P2.54mm_Horizontal
R1, R2, R3, R4: 0; R_1206_3216Metric
U1, U3: MS5803-05BA; TE_MS5803-05BA
U2, U4: MS5607-02BA03; TE_MS5607-02BA03

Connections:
+3V3: C1.2, C2.2, C3.2, C4.2, J3.4, J6.4, R2.1, R4.1, U1.5, U1.6, U2.1, U2.2, U3.5, U3.6, U4.1, U4.2
/Sensors (FPGA)/SCL: J3.3, U1.1, U2.8
/Sensors (FPGA)/SDA: J3.1, U1.7, U2.4
/Sensors (RPi)/SCL: J6.3, U3.1, U4.8
/Sensors (RPi)/SDA: J6.1, U3.7, U4.4
GND: C1.1, C2.1, C3.1, C4.1, J3.2, J3.5, J3.6, J6.2, J6.5, J6.6, R1.2, R3.2, U1.2, U2.3, U3.2, U4.3
unnamed: R1.1, U1.3
unnamed: R2.2, U2.5
unnamed: R3.1, U3.3
unnamed: R4.2, U4.5
